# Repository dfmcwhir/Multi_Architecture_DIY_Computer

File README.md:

# Multi_Architecture_DIY_Computer
A DIY computer system that uses a common backplane with swappable 8-bit CPU and add-on cards<BR><br>
<p>PCB for the cards have I have already made and tested are available on PCBWay here:
https://www.pcbway.com/project/member/shareproject/?bmbno=88AAB50F-5E23-43</p>

Up front, I will state the following:
  1. I started the project for my own learning and enjoyment. There will be documentation shortfalls and hardware and SW bugs that I missed and/or fixed and forgot about. There will also be plenty of poor design choices and probletunities for improvement. 
  2. Most of the electrical designs borrow ideas/circuits from other peoples work and I have modified them to work in my systems. I will try to make sure I document where I got what from.
  3. For the software and firmware, initially I was doing my own development, but I'm not a coder so I progress was really slow/non-existent. More recently, I have started using AI which has led to a lot of progress. Really all the software and firmware in this project is either a slight modifications of other people's code or done by AI.

<br>
<h2> The Concept </h2>
The initial idea as I wrote it in my notes app was:<br>
<quote>
  <b><i></i>Idea for a retro computer "system" that uses various cards in the ISA format with a passive ISA back plane. Ideally the most of the individual ISA cards will be less that 100mmx100mm for cheaper PCB prices which limits them to 8-bit isa cards.

Ideally cpu and interface cards should be inter changeable, so that interface cards can be used with multiple different types of CPU boards. That may require jumpers/switches to change logic level of some control signals and/or to set address decoding.

Possible CPU cards:
  - 6502 - Based on Ben Eater's design
  - 8085 - Similar to the MiniMax 8085?
  - 8088 - IBM XT compatible-ish
  - 6809 - based on Grant Searle's design 
  - Z80 - TRS-80 compatible?
  - ESP32 - For giggles - Would need some sort of multiplexing/latching to generate the data, address, and control busses from the GPIO pins
  - ATMEGA328? - For giggles - Would need some sort of multiplexing/latching to generate the data, address, and control busses from the GPIO pins 

Possible interface cards:
  - Retro video card - MC6847 based. Similar to Kiran Tomlinson's blog post
  - Atmel based keyboard/display/serial - Based on Grant Searle's design
  - Memory expansion
  - Storage controller - ideally the overall system would be compatible with the PicoMem I/O card but a dedicated storage controller maybe required/desired.
</b></i>
</quote>
<br>
So far I have done the 6502 and 8085 CPU cards with the Z80 on the way. The plans for the add-cards changed over time, I didn't do all the ones listed (yet), but I have a number of others. Most of them have ISA_6502 in the name, because that is the CPU I started with, but should at least theoretically be compatible with other CPU cards if they are designed to interface with the bus as I have defined it and with the correct software.

<h2> The "ISA" Bus </h2>
<p>To make it very clear, I am using the physical ISA bus for interfacing but in no way indicating that it meets any ISA specification or standards. Putting a normal ISA card into the system will almost definitely not work and may damage everything. </p>
<p>With that out of the way, when I started designing the system, I tried to match the functions of the signals of my card to the signals functions/names of the standard ISA bus. The idea being, that it would make it easier to insure CPU card compatibility with the add-on cards that way. The matching to the standard ISA pin functions has drifted over time.</p>

<H2>Current bus description</H2>
<table><thead><tr><th>Pin</th><th>Name</th><th>Dir</th><th>Description</th></tr></thead><tbody>
<tr><td>A1</td><td>/I/O CH CK</td><td>IN</td><td>/IOen. Active low; indicates an I/O operation</td></tr>
<tr><td>A2</td><td>D7</td><td>IN/OUT</td><td>Data bit 7</td></tr>
<tr><td>A3</td><td>D6</td><td>IN/OUT</td><td>Data bit 6</td></tr>
<tr><td>A4</td><td>D5</td><td>IN/OUT</td><td>Data bit 5</td></tr>
<tr><td>A5</td><td>D4</td><td>IN/OUT</td><td>Data bit 4</td></tr>
<tr><td>A6</td><td>D3</td><td>IN/OUT</td><td>Data bit 3</td></tr>
<tr><td>A7</td><td>D2</td><td>IN/OUT</td><td>Data bit 2</td></tr>
<tr><td>A8</td><td>D1</td><td>IN/OUT</td><td>Data bit 1</td></tr>
<tr><td>A9</td><td>D0</td><td>IN/OUT&gt;</td><td>Data bit 0</td></tr>
<tr><td>A10</td><td>I/O CH RDY</td><td>IN</td><td>IOrdy or /WAIT, pulled low to lengthen memory cycles or pause the CPU (depending on the CPU card)*</td></tr>
<tr><td>A11</td><td>AEN</td><td>OUT</td><td>Address enable; Not currently used</td></tr>
<tr><td>A12</td><td>A19</td><td>OUT</td><td>Address bit 19 or BA19; Used for memory bank selection</td></tr>
<tr><td>A13</td><td>A18</td><td>OUT</td><td>Address bit 18 or BA18; Used for memory bank selection</td></tr>
<tr><td>A14</td><td>A17</td><td>OUT</td><td>Address bit 17 or BA17; Used for memory bank selection</td></tr>
<tr><td>A15</td><td>A16</td><td>OUT</td><td>Address bit 16 or BA19; Used for memory bank selection</td></tr>
<tr><td>A16</td><td>A15</td><td>OUT</td><td>Address bit 15</td></tr>
<tr><td>A17</td><td>A14</td><td>OUT</td><td>Address bit 14</td></tr>
<tr><td>A18</td><td>A13</td><td>OUT</td><td>Address bit 13</td></tr>
<tr><td>A19</td><td>A12</td><td>OUT</td><td>Address bit 12</td></tr>
<tr><td>A20</td><td>A11</td><td>OUT</td><td>Address bit 11</td></tr>
<tr><td>A21</td><td>A10</td><td>OUT</td><td>Address bit 10</td></tr>
<tr><td>A22</td><td>A9</td><td>OUT</td><td>Address bit 9</td></tr>
<tr><td>A23</td><td>A8</td><td>OUT</td><td>Address bit 8</td></tr>
<tr><td>A24</td><td>A7</td><td>OUT</td><td>Address bit 7</td></tr>
<tr><td>A25</td><td>A6</td><td>OUT</td><td>Address bit 6</td></tr>
<tr><td>A26</td><td>A5</td><td>OUT</td><td>Address bit 5</td></tr>
<tr><td>A27</td><td>A4</td><td>OUT</td><td>Address bit 4</td></tr>
<tr><td>A28</td><td>A3</td><td>OUT</td><td>Address bit 3</td></tr>
<tr><td>A29</td><td>A2</td><td>OUT</td><td>Address bit 2</td></tr>
<tr><td>A30</td><td>A1</td><td>OUT</td><td>Address bit 1</td></tr>
<tr><td>A31</td><td>A0</td><td>OUT</td><td>Address bit 0</td></tr>
<tr><td>B1</td><td><abbr title="Ground">GND</abbr></td><td>Ground</td><td></td>
</tr><tr><td>B2</td><td>RESET</td><td>OUT</td><td>Active low to reset or initialize system logic</td></tr>
<tr><td>B3</td><td>+5V</td><td>+5 <abbr title="Volts Direct Current">VDC</abbr></td><td></td></tr>
<tr><td>B4</td><td>IRQ2</td><td>IN</td><td>Interrupt Request 2; I/O card </td></tr>
<tr><td>B5</td><td>-5VDC</td><td>-5 VDC</td><td>Not Currently used</td></tr>
<tr><td>B6</td><td>DRQ2</td><td>IN</td><td>/DMA; Not used/tested by any add-on cards yet, but should put CPU in state for DMA operations*</td></tr>
<tr><td>B7</td><td>-12VDC</td><td>-12 VDC</td><td>Not Currently used</td></tr>
<tr><td>B8</td><td>/NOWS</td><td>IN</td><td>/STRETCH (CLK stretch); When Low should slow down the clock*</td></tr>
<tr><td>B9</td><td>+12VDC</td><td>+12 VDC</td><td>Not Currently used</td></tr>
<tr><td>B10</td><td>GND</td><td>Ground</td><td></td></tr>
<tr><td>B11</td><td>/SMEMW</td><td>OUT</td><td>Originally intended as /MEMw, but may now be a general Write*</td></tr>
<tr><td>B12</td><td>/SMEMR</td><td>OUT</td><td>Originally intended as /MEMr, but may now be a general Read*</td></tr>
<tr><td>B13</td><td>/IOW</td><td>OUT</td><td>/IOw (/IOen + /Write)*</td></tr>
<tr><td>B14</td><td>/IOR</td><td>OUT</td><td>/IOr (/IOen + /Read + Clk)*</td></tr>
<tr><td>B15</td><td>/DACK3</td><td>OUT</td><td>Not currently used</td></tr>
<tr><td>B16</td><td>DRQ3</td><td>IN</td><td>Not currently used</td></tr>
<tr><td>B17</td><td>/DACK1</td><td>OUT</td><td>Not currently used</td></tr>
<tr><td>B18</td><td>DRQ1</td><td>IN</td><td>Not currently used</td></tr>
<tr><td>B19</td><td>/REFRESH</td><td>IN/OUT</td><td>Not currently used</td></tr>
<tr><td>B20</td><td>CLOCK</td><td>OUT</td><td>/CLK (inverted clock)</td></tr>
<tr><td>B21</td><td>IRQ7</td><td>IN</td><td>Interrupt Request 7, Possibly sound card or SPI interface</td></tr>
<tr><td>B22</td><td>IRQ6</td><td>IN</td><td>Interrupt Request 6; Possibly display/kb</td></tr>
<tr><td>B23</td><td>IRQ5</td><td>IN</td><td>Interrupt Request 5; Usually KB/Display</td></tr>
<tr><td>B24</td><td>IRQ4</td><td>IN</td><td>Interrupt Request 4; I/O card I2C interface</td></tr>
<tr><td>B25</td><td>IRQ3</td><td>IN</td><td>Interrupt Request 3; Serial Card</td></tr>
<tr><td>B26</td><td>/DACK2</td><td>OUT</td><td>Not currently used</td></tr>
<tr><td>B27</td><td>T/C</td><td>OUT</td><td>Raw oscilator clock (2 x CLK) on some CPU cards(</td></tr>
<tr><td>B28</td><td>ALE</td><td>OUT</td><td>Not currently used</td></tr>
<tr><td>B29</td><td>+5V</td><td>+5 VDC</td><td></td></tr>
<tr><td>B30</td><td>OSC</td><td>OUT</td><td>CLK used by CPU and most circuits. In some CPU cards it is 1/2 of the osc frequency</td></tr>
<tr><td>B31</td><td>GND</td><td>Ground</td><td></td></tr>
<tr><td></td><td></td><td></td><td></td></tr>
</tbody></table>
<h3>Notes about some signals:</h3>
<p> /MEMw and /MEMr were initially derived from the R/nW signal on the 6502 card and either /ROMen or /RAMen. As things got more complex, it became necessary to have read and write signals that were available during I/O operations (/IOen) but were not connected to the clock. So now /MEMw and /MEMr on the bus could (depending on the CPU card) be active anytime either an I/O or Memory operation is happening. This means that add-on cards, if a memory read or write is needed, the /MEMw and MEMr signals should be qualified as being in memory by the address or at least by /IOen not being active.</p>
<p>The way /IOr is used on some add-on cards requires it to be active only when the CLK is high, so that is the way it is decoded on the bus. If a read from I/O that isn't dependent on the CLK being high is required (also required on some cards) then a local /read should be decoded from the /IOen and MEMr or /IOen and /IOw not active. /IOw is independent from the clk</p>
<p>Initially the /DMA (/DRQ2) signal was provided for simple DMA operations that Ben Eater describes for his VGA card implementaion. I have never used it and it maybe incompatible with some CPU cards.</p>
<p>IOrdy (or /WAIT) and /STRETCH were implemented on the 6502 CPU Rev2 card and haven't been tested yet. The difference is that /WAIT stops the CPU but CLK and /CLK continue to run. /Stretch stops CLK and /CLK. An Add-card would assert /Stretch then use the TC (2XOSC) raw oscillator signal to count some number of cycles before de-asserting it. On some CPU cards neither signal is implemented at all (like the 8085 CPU Rev1) and on others (like the Z80 CPU rev1) /STRETCH and /WAIT are the same (both are /STRETCH). I don't think any cards require these signals/features if operated at <4MHz. </p>

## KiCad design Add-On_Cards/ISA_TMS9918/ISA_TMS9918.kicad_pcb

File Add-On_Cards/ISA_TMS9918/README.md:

<h2>ISA_TMS9918</h2>

<p>This is a new card that hasn't been built or tested yet. It is designed around the old TMS9918A chip and outputs composite video for a more retro feel. Or, most of the components can be left off and a PICO9918 can be used for VGA or HDMI output. Also, as a test, two TMS cards can be connected together to increase the graphics capabilities. This is allowed per the TMS9918 datasheet, but it may (likely?) will not work in this implementation. To link the two cards together it requires both cards to be clocked by the same clock. Probably the best way of doing that would be to use an oscillator and run that through a buffer and an inverter to the XTAL1 and XTAL2 inputs for both TMS9918 chips (the XTAL1 and XTAL2 inputs apparently need inverses of each other from my research), but I couldn't find a through hole oscillator of the correct frequency, so basically this card has a header that can connect the crystal pins to both chip's XTAL pins (which is actually what the datasheet shows), but I don't know if that will work or if the whole setup will be too noisy. It is an experiment. If it doesn't work then it should still work as a stand alone card and the dual card concept can be revisited later.</p>

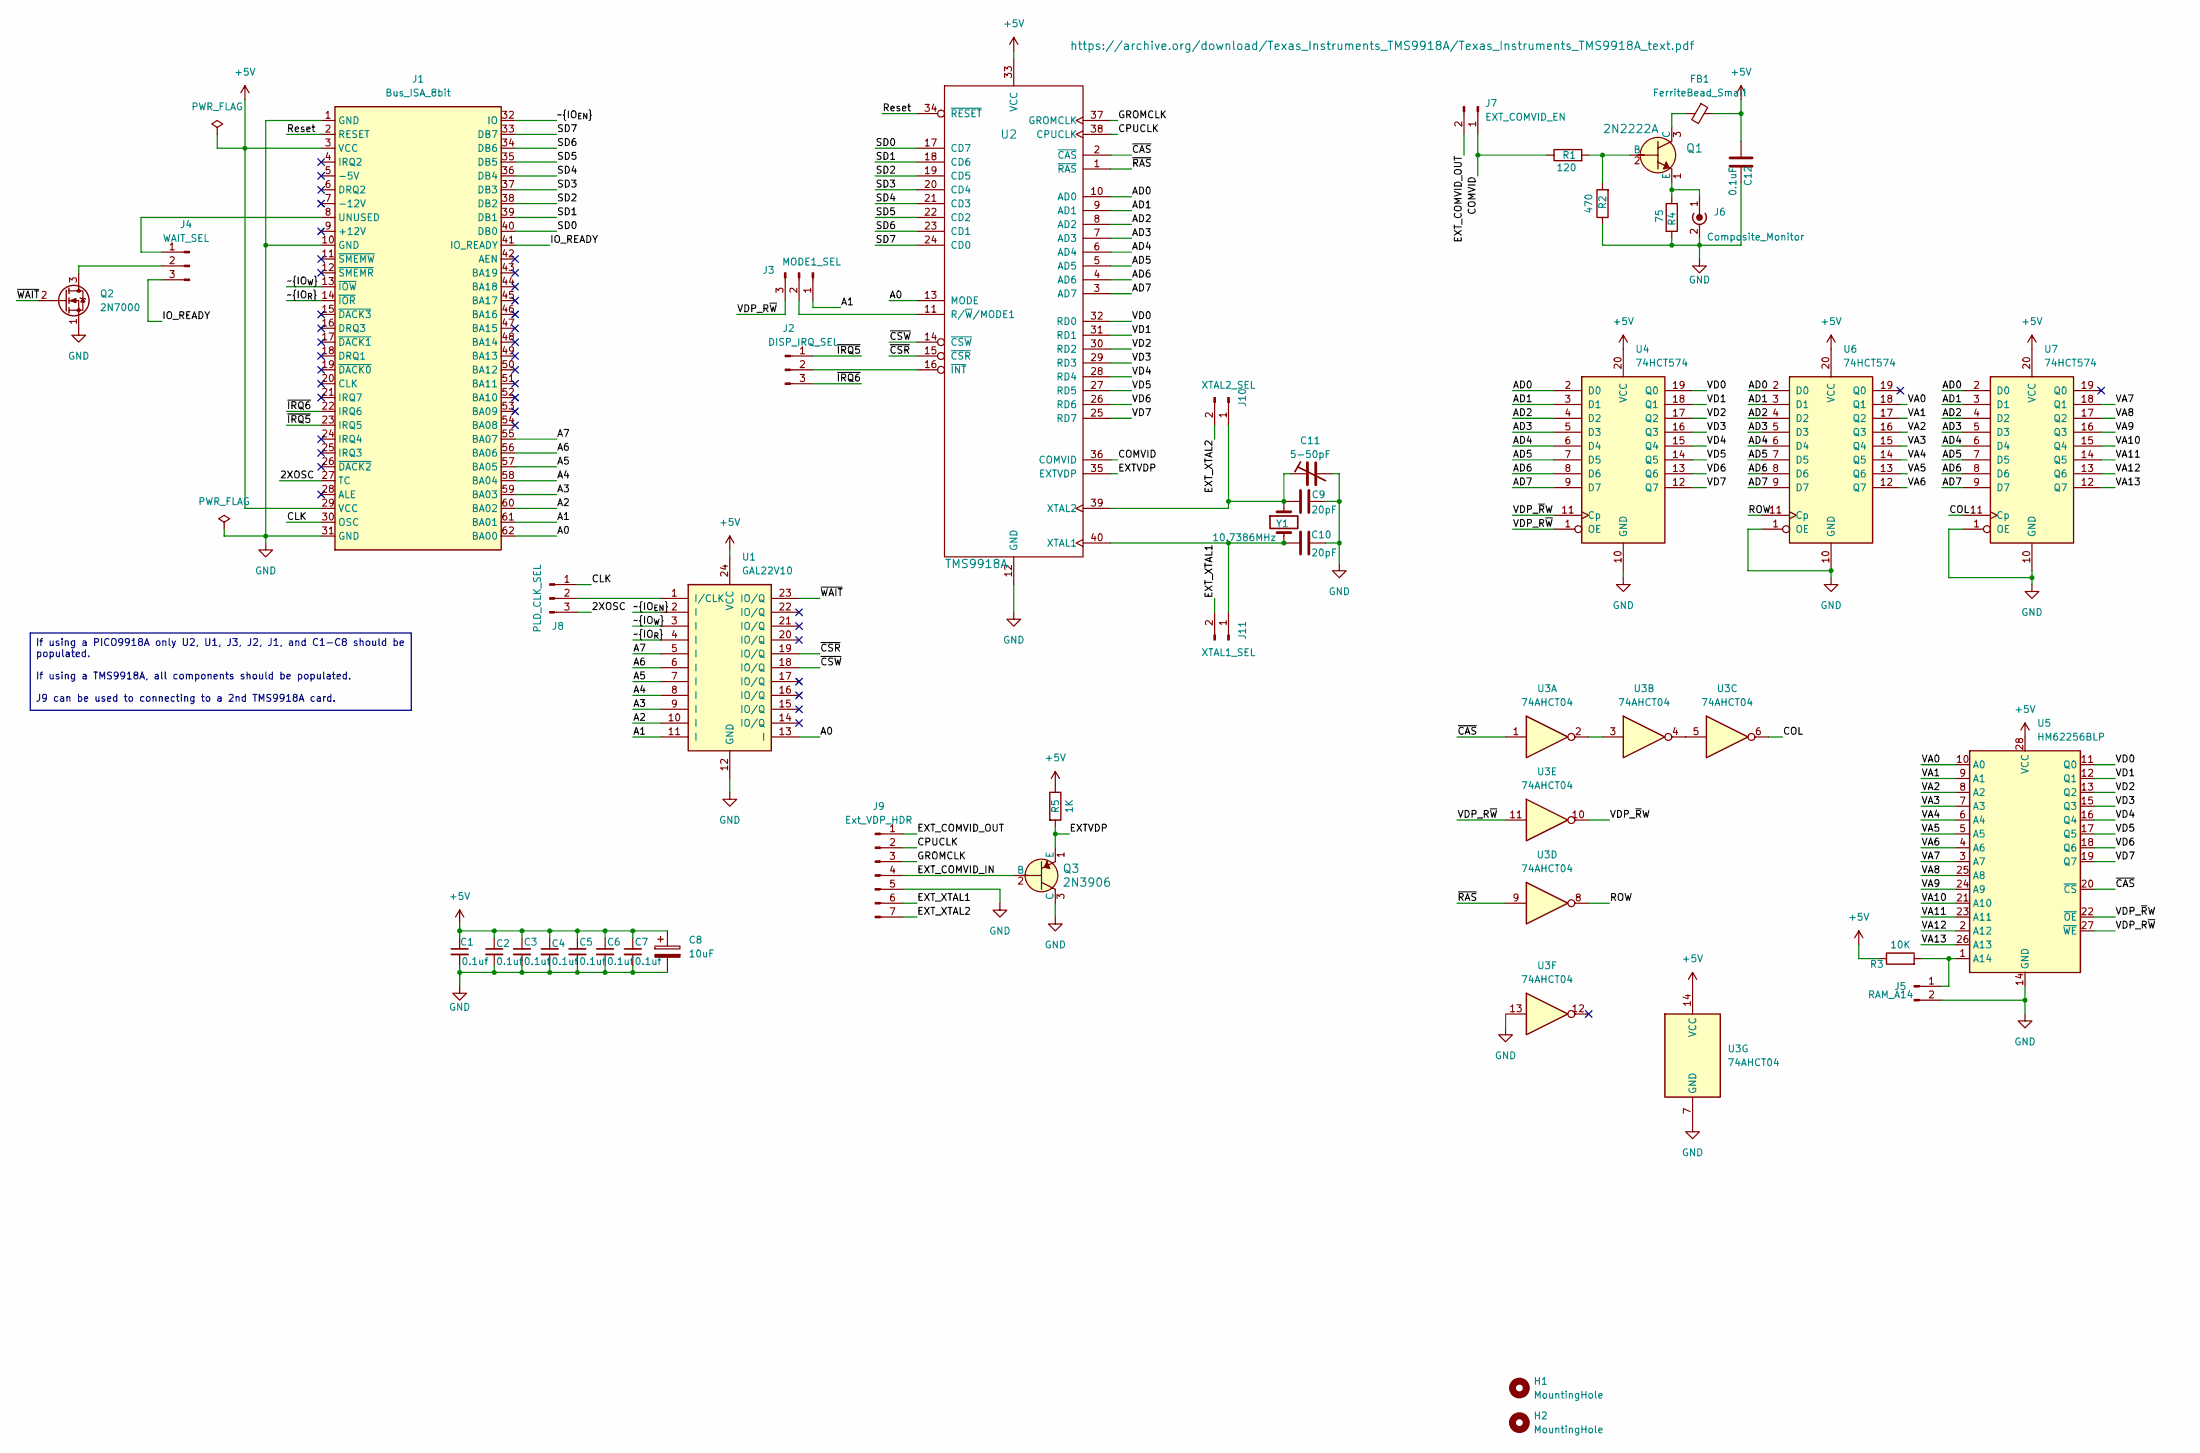
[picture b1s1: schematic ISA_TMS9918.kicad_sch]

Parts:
C1, C2, C3, C4, C5, C6, C7: 0.1uf; C_Disc_D4.7mm_W2.5mm_P5.00mm; Voltage 50V; Tolerance 5%
C8: 10uF; CP_Radial_D5.0mm_P2.00mm
C9, C10: 20pF; C_Disc_D4.7mm_W2.5mm_P5.00mm
C11: 5-50pF; CP_Radial_D8.0mm_P5.00mm
C12: 0.1uF; C_Disc_D4.7mm_W2.5mm_P5.00mm
FB1: FerriteBead_Small; R_Axial_DIN0207_L6.3mm_D2.5mm_P10.16mm_Horizontal
H1, H2: MountingHole; MountingHole_3.2mm_M3
J1: Bus_ISA_8bit; BUS_8-bit_ISA_CARD
J2: DISP_IRQ_SEL; PinHeader_1x03_P2.54mm_Vertical
J3: MODE1_SEL; PinHeader_1x03_P2.54mm_Vertical
J4: WAIT_SEL; PinHeader_1x03_P2.54mm_Vertical
J5: RAM_A14; PinHeader_1x02_P2.54mm_Vertical
J6: Composite_Monitor; RCA_JACK_Right_Angle_AliExpress
J7: EXT_COMVID_EN; PinHeader_1x02_P2.54mm_Vertical
J8: PLD_CLK_SEL; PinHeader_1x03_P2.54mm_Vertical
J9: Ext_VDP_HDR; PinHeader_1x07_P2.54mm_Vertical
J10: XTAL2_SEL; PinHeader_1x02_P2.54mm_Vertical
J11: XTAL1_SEL; PinHeader_1x02_P2.54mm_Vertical
Q1: 2N2222A; TO-92L_Wide; MPN 2N2222A; Digi-Key_PN 2N2222ACS-ND
Q2: 2N7000; TO-92L_Wide
Q3: 2N3906; TO-92L_Wide; MPN 2N3906; Digi-Key_PN 2N3906CS-ND
R1: 120; R_Axial_DIN0207_L6.3mm_D2.5mm_P10.16mm_Horizontal
R2: 470; R_Axial_DIN0207_L6.3mm_D2.5mm_P10.16mm_Horizontal
R3: 10K; R_Axial_DIN0207_L6.3mm_D2.5mm_P10.16mm_Horizontal
R4: 75; R_Axial_DIN0207_L6.3mm_D2.5mm_P10.16mm_Horizontal
R5: 1K; R_Axial_DIN0207_L6.3mm_D2.5mm_P10.16mm_Horizontal
U1: GAL22V10; DIP-24_W7.62mm
U2: TMS9918A; DIP-40_W15.24mm
U3: 74AHCT04; DIP-14_W7.62mm
U4, U6, U7: 74HCT574; DIP-20_W7.62mm
U5: HM62256BLP; DIP-28_W15.24mm
Y1: 10.7386MHz; Crystal_HC49-U_Horizontal

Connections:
+5V: C1.1, C2.1, C3.1, C4.1, C5.1, C6.1, C7.1, C8.1, C12.1, FB1.1, J1.3 (VCC), J1.29 (VCC), R3.1, R5.1, U1.24 (VCC), U2.33 (VCC), U3.14 (VCC), U4.20 (VCC), U5.28 (VCC), U6.20 (VCC), U7.20 (VCC)
/2XOSC: J1.27 (TC), J8.3
/A0: J1.62 (BA00), U1.13 (I), U2.13 (MODE)
/A1: J1.61 (BA01), J3.1, U1.11 (I)
/A2: J1.60 (BA02), U1.10 (I)
/A3: J1.59 (BA03), U1.9 (I)
/A4: J1.58 (BA04), U1.8 (I)
/A5: J1.57 (BA05), U1.7 (I)
/A6: J1.56 (BA06), U1.6 (I)
/A7: J1.55 (BA07), U1.5 (I)
/AD0: U2.10 (AD0), U4.2 (D0), U6.2 (D0), U7.2 (D0)
/AD1: U2.9 (AD1), U4.3 (D1), U6.3 (D1), U7.3 (D1)
/AD2: U2.8 (AD2), U4.4 (D2), U6.4 (D2), U7.4 (D2)
/AD3: U2.7 (AD3), U4.5 (D3), U6.5 (D3), U7.5 (D3)
/AD4: U2.6 (AD4), U4.6 (D4), U6.6 (D4), U7.6 (D4)
/AD5: U2.5 (AD5), U4.7 (D5), U6.7 (D5), U7.7 (D5)
/AD6: U2.4 (AD6), U4.8 (D6), U6.8 (D6), U7.8 (D6)
/AD7: U2.3 (AD7), U4.9 (D7), U6.9 (D7), U7.9 (D7)
/CLK: J1.30 (OSC), J8.1
/COL: U3.6, U7.11 (Cp)
/COMVID: J7.1, R1.1, U2.36 (COMVID)
/CPUCLK: J9.2, U2.38 (CPUCLK)
/EXTVDP: Q3.1 (E), R5.2, U2.35 (EXTVDP)
/EXT_COMVID_IN: J9.4, Q3.2 (B)
/EXT_COMVID_OUT: J7.2, J9.1
/EXT_XTAL1: J9.6, J11.2
/EXT_XTAL2: J9.7, J10.2
/GROMCLK: J9.3, U2.37 (GROMCLK)
/IO_READY: J1.41 (IO_READY), J4.3
/ROW: U3.8, U6.11 (Cp)
/Reset: J1.2 (RESET), U2.34 (~RESET)
/SD0: J1.40 (DB0), U2.17 (CD7)
/SD1: J1.39 (DB1), U2.18 (CD6)
/SD2: J1.38 (DB2), U2.19 (CD5)
/SD3: J1.37 (DB3), U2.20 (CD4)
/SD4: J1.36 (DB4), U2.21 (CD3)
/SD5: J1.35 (DB5), U2.22 (CD2)
/SD6: J1.34 (DB6), U2.23 (CD1)
/SD7: J1.33 (DB7), U2.24 (CD0)
/VA0: U5.10 (A0), U6.18 (Q1)
/VA1: U5.9 (A1), U6.17 (Q2)
/VA2: U5.8 (A2), U6.16 (Q3)
/VA3: U5.7 (A3), U6.15 (Q4)
/VA4: U5.6 (A4), U6.14 (Q5)
/VA5: U5.5 (A5), U6.13 (Q6)
/VA6: U5.4 (A6), U6.12 (Q7)
/VA7: U5.3 (A7), U7.18 (Q1)
/VA8: U5.25 (A8), U7.17 (Q2)
/VA9: U5.24 (A9), U7.16 (Q3)
/VA10: U5.21 (A10), U7.15 (Q4)
/VA11: U5.23 (A11), U7.14 (Q5)
/VA12: U5.2 (A12), U7.13 (Q6)
/VA13: U5.26 (A13), U7.12 (Q7)
/VD0: U2.32 (RD0), U4.19 (Q0), U5.11 (Q0)
/VD1: U2.31 (RD1), U4.18 (Q1), U5.12 (Q1)
/VD2: U2.30 (RD2), U4.17 (Q2), U5.13 (Q2)
/VD3: U2.29 (RD3), U4.16 (Q3), U5.15 (Q3)
/VD4: U2.28 (RD4), U4.15 (Q4), U5.16 (Q4)
/VD5: U2.27 (RD5), U4.14 (Q5), U5.17 (Q5)
/VD6: U2.26 (RD6), U4.13 (Q6), U5.18 (Q6)
/VD7: U2.25 (RD7), U4.12 (Q7), U5.19 (Q7)
/VDP_R~W: J3.3, U3.11, U4.1 (OE), U5.27 (~WE)
/VDP_~RW: U3.10, U4.11 (Cp), U5.22 (~OE)
/~CAS: U2.2 (~CAS), U3.1, U5.20 (~CS)
/~CSR: U1.19 (IO/Q), U2.15 (~CSR)
/~CSW: U1.18 (IO/Q), U2.14 (~CSW)
/~IO_{EN}: J1.32 (IO), U1.2 (I)
/~IO_{R}: J1.14 (~IOR), U1.4 (I)
/~IO_{W}: J1.13 (~IOW), U1.3 (I)
/~IRQ5: J1.23 (IRQ5), J2.1
/~IRQ6: J1.22 (IRQ6), J2.3
/~RAS: U2.1 (~RAS), U3.9
/~WAIT: Q2.2 (G), U1.23 (IO/Q)
GND: C1.2, C2.2, C3.2, C4.2, C5.2, C6.2, C7.2, C8.2, C9.2, C10.2, C11.2, C12.2, J1.1 (GND), J1.10 (GND), J1.31 (GND), J5.2, J6.2 (Ext), J9.5, Q2.1 (S), Q3.3 (C), R2.1, R4.2, U1.12 (GND), U2.12 (GND), U3.7 (GND), U3.13, U4.10 (GND), U5.14 (GND), U6.1 (OE), U6.10 (GND), U7.1 (OE), U7.10 (GND)
unnamed: J1.8 (UNUSED), J4.1
unnamed: J2.2, U2.16 (~INT)
unnamed: J3.2, U2.11 (R/~W/MODE1)
unnamed: J4.2, Q2.3 (D)
unnamed: J5.1, R3.2, U5.1 (A14)
unnamed: J6.1 (In), Q1.1 (E), R4.1
unnamed: J8.2, U1.1 (I/CLK)
unnamed: C9.1, C11.1, J10.1, U2.39 (XTAL2), Y1.1
unnamed: C10.1, J11.1, U2.40 (XTAL1), Y1.2
unnamed: Q1.2 (B), R1.2, R2.2
unnamed: FB1.2, Q1.3 (C)
unnamed: U3.2, U3.3
unnamed: U3.4, U3.5

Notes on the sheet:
If using a PICO9918A only U2, U1, J3, J2, J1, and C1-C8 should be populated. If using a TMS9918A, all components should be populated. J9 can be used to connecting to a 2nd TMS9918A card.

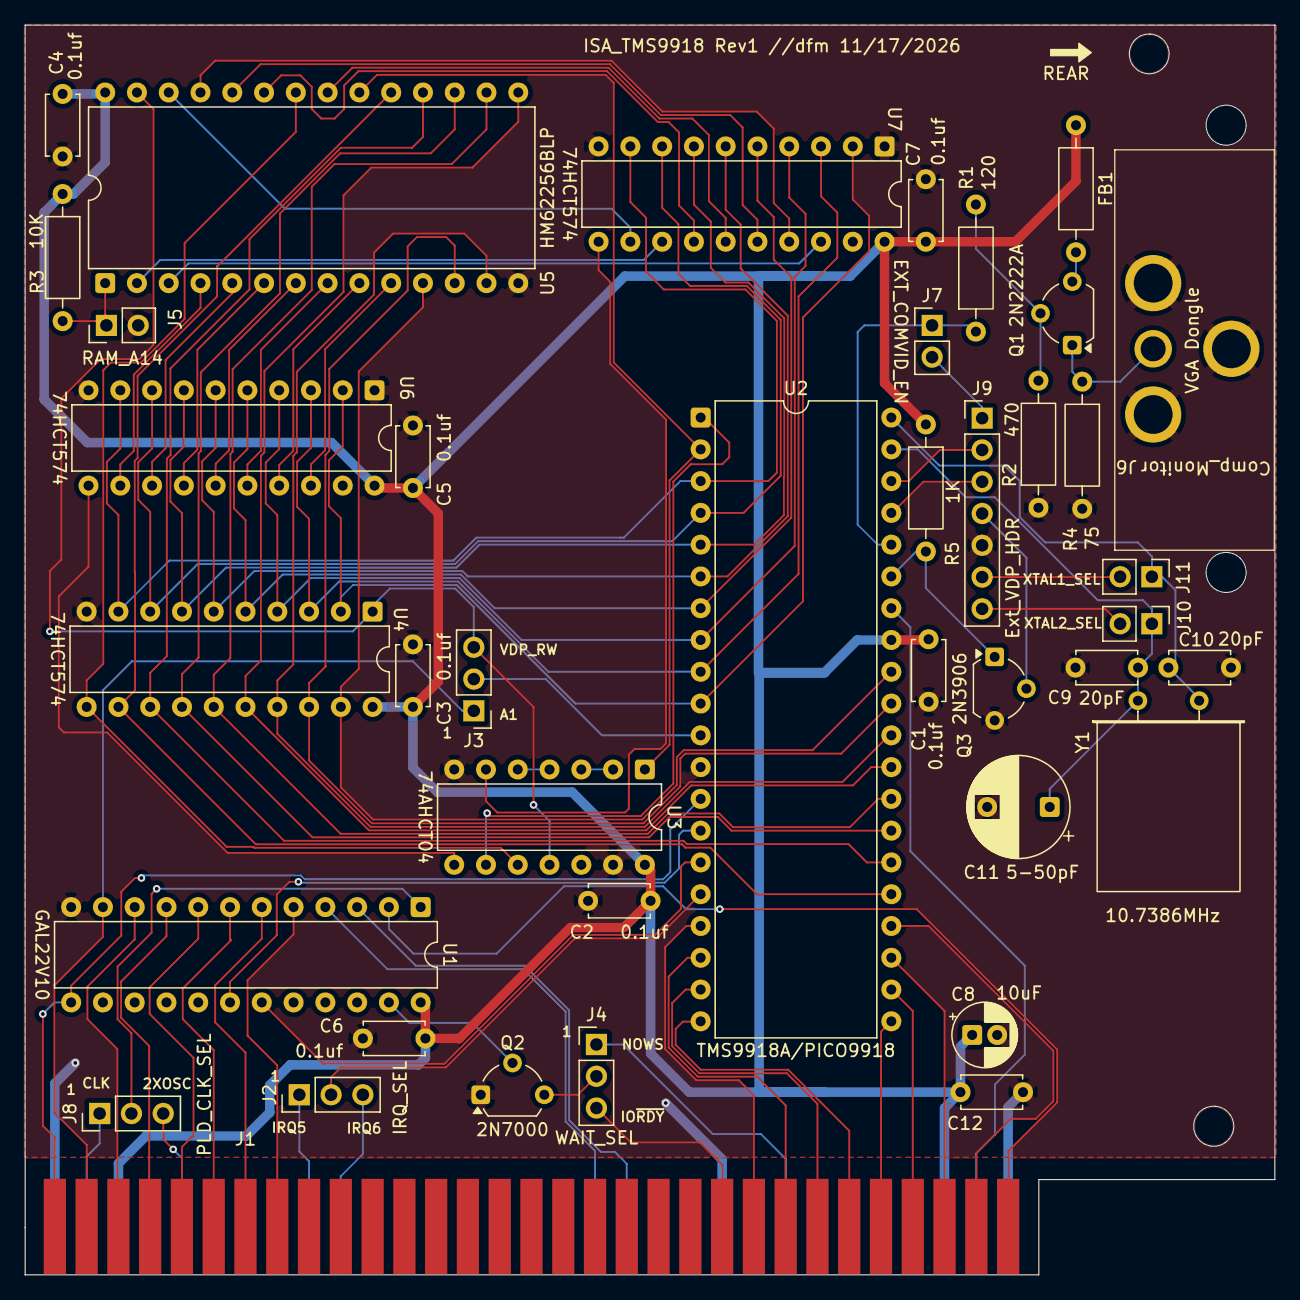
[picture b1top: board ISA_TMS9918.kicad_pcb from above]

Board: 2 copper layers, 99.9 x 99.9 mm, 42 parts (0 on the bottom side), 87 nets.

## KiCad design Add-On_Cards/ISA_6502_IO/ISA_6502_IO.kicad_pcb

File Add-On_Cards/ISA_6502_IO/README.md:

<h1> ISA_6502_IO card</h1>
<p>6522 based IO card. Also has PCF8584 I2C interface. Primarily used for timers for the sound card routines and interface for the NES gamepad, so it is required for a lot of games and software.</p>

<h2>Known Bugs</h2>
  <li>The footprints for the resistors are too small so they have to be installed at an angle. </li>
  <li>The PCF8584 has jumpers to connect the SDA and SCL I2C signals to the bus on what were previously unused pins. Those pins are now used for other signals, so those jumpers should never be installed. The I2C interface is still available on the header pins on the card.</li>

<h2>Resources</h2>
<table><thead><tr><th>Address</th><th>Function</th></tr></thead>
<tr><td>7F00</td><td>PORTB</td></tr>
<tr><td>7F01</td><td>PORTA</td></tr>
<tr><td>7F02</td><td>DDRB</td></tr>
<tr><td>7F03</td><td>DDRA</td></tr>
<tr><td>7F04</td><td>T1C LOW</td></tr>
<tr><td>7F05</td><td>T1C HIGH</td></tr>
<tr><td>7F06</td><td>T1L LOW</td></tr>
<tr><td>7F07</td><td>T1L HIGH</td></tr>
<tr><td>7F08</td><td>T2C LOW</td></tr>
<tr><td>7F09</td><td>T2C HIGH</td></tr>
<tr><td>7F0A</td><td>SR</td></tr>
<tr><td>7F0B</td><td>ACR</td></tr>
<tr><td>7F0C</td><td>PCR</td></tr>
<tr><td>7F0D</td><td>IFR</td></tr>
<tr><td>7F0E</td><td>IER</td></tr>
<tr><td>7F0F</td><td>ORA/IRA</td></tr>
</table>

6522 = IRQ2<br>
PCF8584 = IRQ4

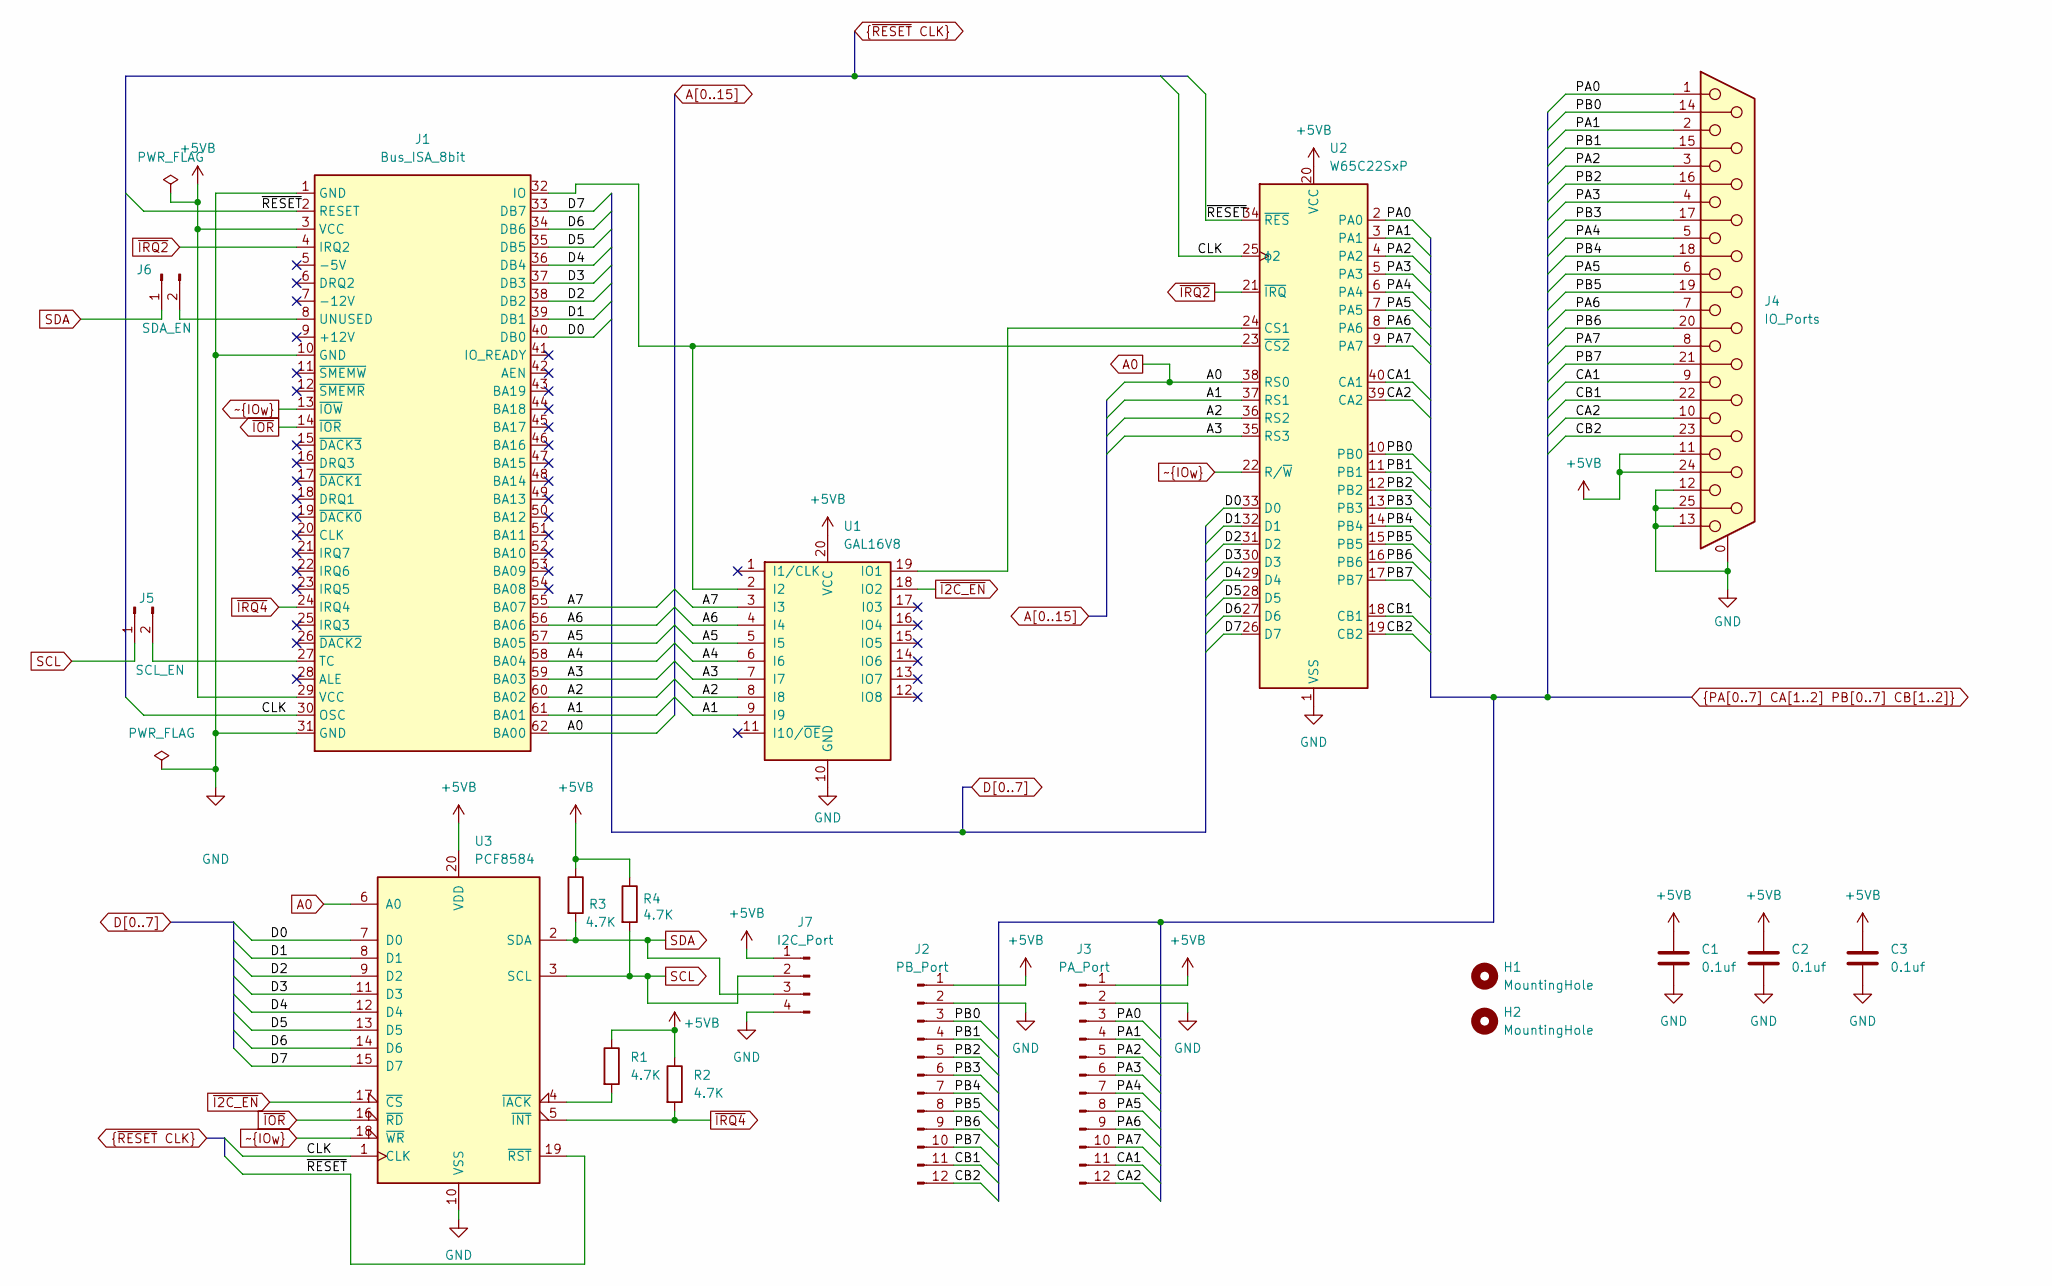
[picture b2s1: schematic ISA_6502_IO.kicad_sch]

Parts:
C1, C2, C3: 0.1uf; C_Disc_D4.7mm_W2.5mm_P5.00mm
H1, H2: MountingHole; MountingHole_3.2mm_M3
J1: Bus_ISA_8bit; BUS_8-bit_ISA
J2: PB_Port; PinHeader_1x12_P2.54mm_Vertical
J3: PA_Port; PinHeader_1x12_P2.54mm_Vertical
J4: IO_Ports; DSUB-25_Socket_Horizontal_P2.77x2.84mm_EdgePinOffset9.90mm_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
J5: SCL_EN; PinHeader_1x02_P2.54mm_Vertical
J6: SDA_EN; PinHeader_1x02_P2.54mm_Vertical
J7: I2C_Port; PinHeader_1x04_P2.54mm_Vertical
R1, R2, R3, R4: 4.7K; R_Axial_DIN0204_L3.6mm_D1.6mm_P5.08mm_Horizontal
U1: GAL16V8; DIP-20_W7.62mm
U2: W65C22SxP; DIP-40_W15.24mm
U3: PCF8584; DIP-20_W7.62mm

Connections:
+5VB: C1.1, C2.1, C3.1, J1.3 (VCC), J1.29 (VCC), J2.1, J3.1, J4.11, J4.24, J7.1, R1.1, R2.1, R3.1, R4.1, U1.20 (VCC), U2.20 (VCC), U3.20 (VDD)
A0: J1.62 (BA00), U2.38 (RS0), U3.6 (A0)
A1: J1.61 (BA01), U1.9 (I9), U2.37 (RS1)
A2: J1.60 (BA02), U1.8 (I8), U2.36 (RS2)
A3: J1.59 (BA03), U1.7 (I7), U2.35 (RS3)
A4: J1.58 (BA04), U1.6 (I6)
A5: J1.57 (BA05), U1.5 (I5)
A6: J1.56 (BA06), U1.4 (I4)
A7: J1.55 (BA07), U1.3 (I3)
CA1: J3.11, J4.9, U2.40 (CA1)
CA2: J3.12, J4.10, U2.39 (CA2)
CB1: J2.11, J4.22, U2.18 (CB1)
CB2: J2.12, J4.23, U2.19 (CB2)
CLK: J1.30 (OSC), U2.25 (ϕ2), U3.1 (CLK)
D0: J1.40 (DB0), U2.33 (D0), U3.7 (D0)
D1: J1.39 (DB1), U2.32 (D1), U3.8 (D1)
D2: J1.38 (DB2), U2.31 (D2), U3.9 (D2)
D3: J1.37 (DB3), U2.30 (D3), U3.11 (D3)
D4: J1.36 (DB4), U2.29 (D4), U3.12 (D4)
D5: J1.35 (DB5), U2.28 (D5), U3.13 (D5)
D6: J1.34 (DB6), U2.27 (D6), U3.14 (D6)
D7: J1.33 (DB7), U2.26 (D7), U3.15 (D7)
GND: C1.2, C2.2, C3.2, J1.1 (GND), J1.10 (GND), J1.31 (GND), J2.2, J3.2, J4.0 (PAD), J4.12, J4.13, J4.25, J7.4, U1.10 (GND), U2.1 (VSS), U3.10 (VSS)
unnamed: J1.32 (IO), U1.2 (I2), U2.23 (~CS2)
unnamed: J1.27 (TC), J5.2
unnamed: J1.8 (UNUSED), J6.2
unnamed: U1.19 (IO1), U2.24 (CS1)
unnamed: R1.2, U3.4 (~IACK)
PA0: J3.3, J4.1, U2.2 (PA0)
PA1: J3.4, J4.2, U2.3 (PA1)
PA2: J3.5, J4.3, U2.4 (PA2)
PA3: J3.6, J4.4, U2.5 (PA3)
PA4: J3.7, J4.5, U2.6 (PA4)
PA5: J3.8, J4.6, U2.7 (PA5)
PA6: J3.9, J4.7, U2.8 (PA6)
PA7: J3.10, J4.8, U2.9 (PA7)
PB0: J2.3, J4.14, U2.10 (PB0)
PB1: J2.4, J4.15, U2.11 (PB1)
PB2: J2.5, J4.16, U2.12 (PB2)
PB3: J2.6, J4.17, U2.13 (PB3)
PB4: J2.7, J4.18, U2.14 (PB4)
PB5: J2.8, J4.19, U2.15 (PB5)
PB6: J2.9, J4.20, U2.16 (PB6)
PB7: J2.10, J4.21, U2.17 (PB7)
SCL: J5.1, J7.2, R4.2, U3.3 (SCL)
SDA: J6.1, J7.3, R3.2, U3.2 (SDA)
~I2C_EN: U1.18 (IO2), U3.17 (~CS)
~IOR: J1.14 (~IOR), U3.16 (~RD)
~IO_{W}: J1.13 (~IOW), U2.22 (R/~W), U3.18 (~WR)
~IRQ2: J1.4 (IRQ2), U2.21 (~IRQ)
~IRQ4: J1.24 (IRQ4), R2.2, U3.5 (~INT)
~RESET: J1.2 (RESET), U2.34 (~RES), U3.19 (~RST)

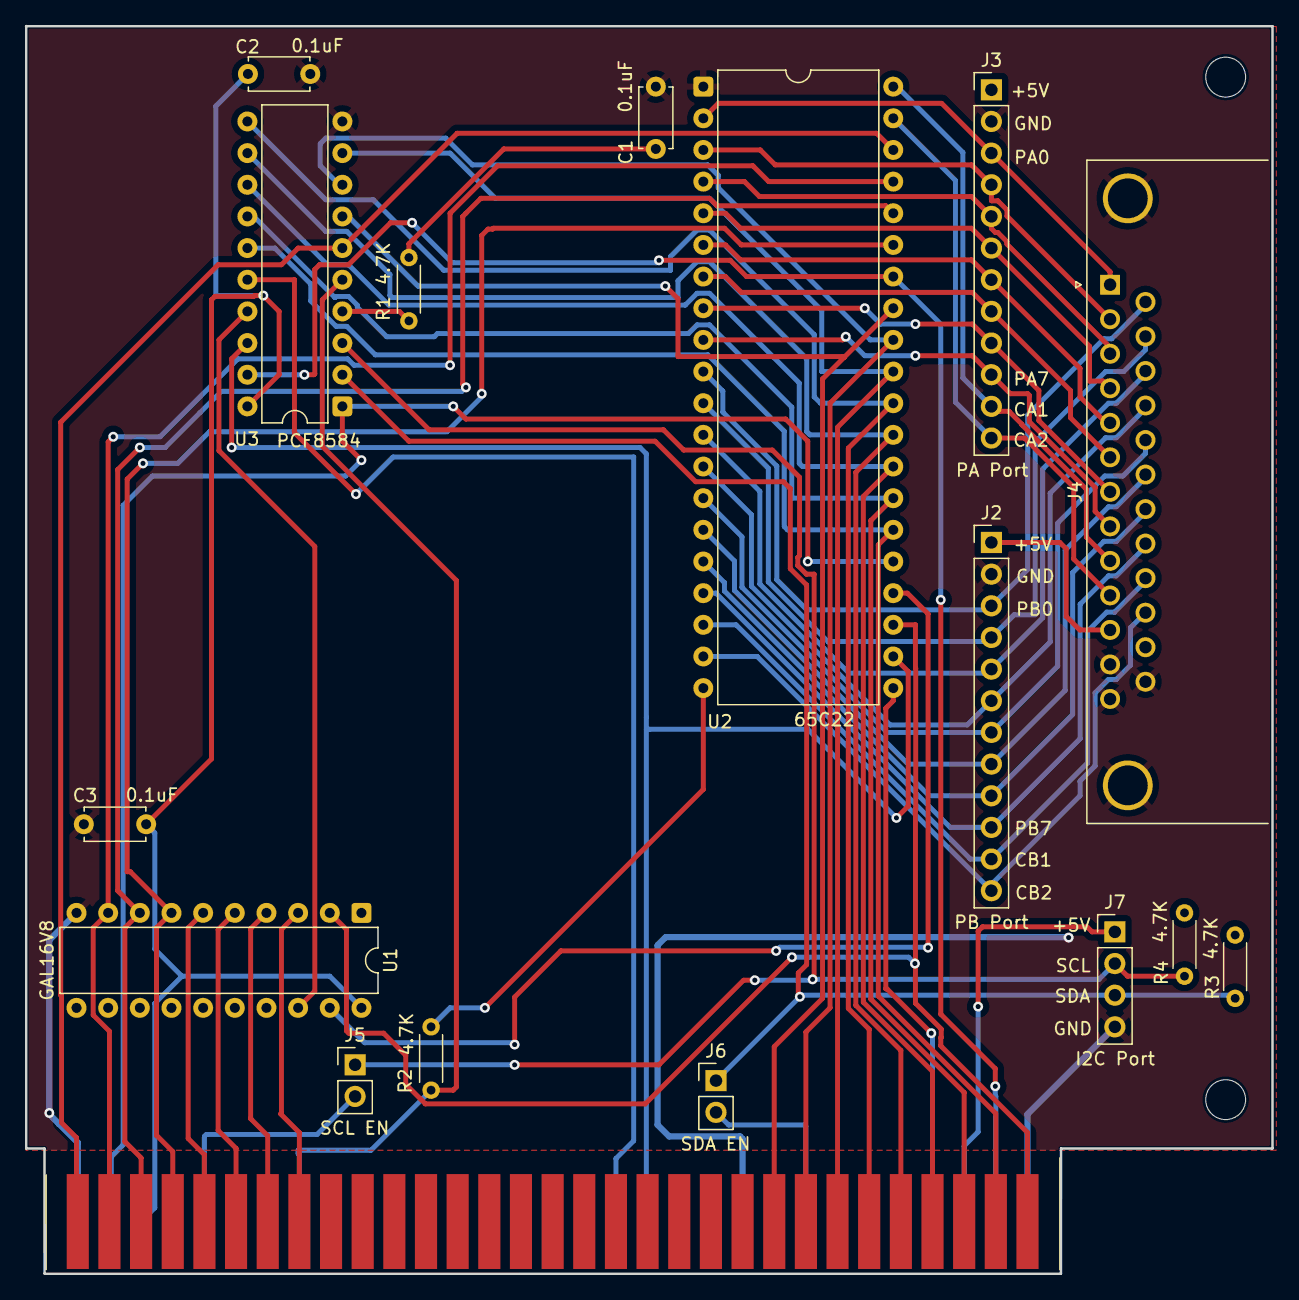
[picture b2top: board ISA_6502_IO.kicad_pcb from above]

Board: 2 copper layers, 100.0 x 100.1 mm, 19 parts (0 on the bottom side), 52 nets.
